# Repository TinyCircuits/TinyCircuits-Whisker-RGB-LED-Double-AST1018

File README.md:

# TinyCircuits Wireling RGB LED
# AST1018 Rev2

The design files are located under design_files/ for the TinyCircuits AST1018 Rev 2 PCB. This is a Wireling board which features the SK6812 Serial RGB LED to add a variety of bright colors to any project. Includes an additional connector for the option of connecting more RGB LED Wirelings.

Format is in Cadsoft Eagle format - Eagle version 6.2 was used for the original design.

For more infomation on this, check out the product page at TinyCircuits.com

# License:

Design by TinyCircuits.
All design files are released under the Creative Commons Attribution Share-Alike 3.0 License, see the following link for details: http://creativecommons.org/licenses/by-sa/3.0

All text above must be included in any redistribution or derived design

This project uses designs and concepts developed as part of the Arduino project and the LilyPad project.  The TinyCircuits design files themselves (schematics, PCB and libraries) are not directly derived from these works' design files and have been created new, however the concepts and basic architecture behind the TinyDuino and TinyLily products are derived and we thank the hard work of the organizations below for their contributions to open-source hardware:
  
Original Arduino Uno Design by Team Arduino

LilyPad Arduino Design by Leah Buechley and Sparkfun Electronics

Please support the open-source hardware community

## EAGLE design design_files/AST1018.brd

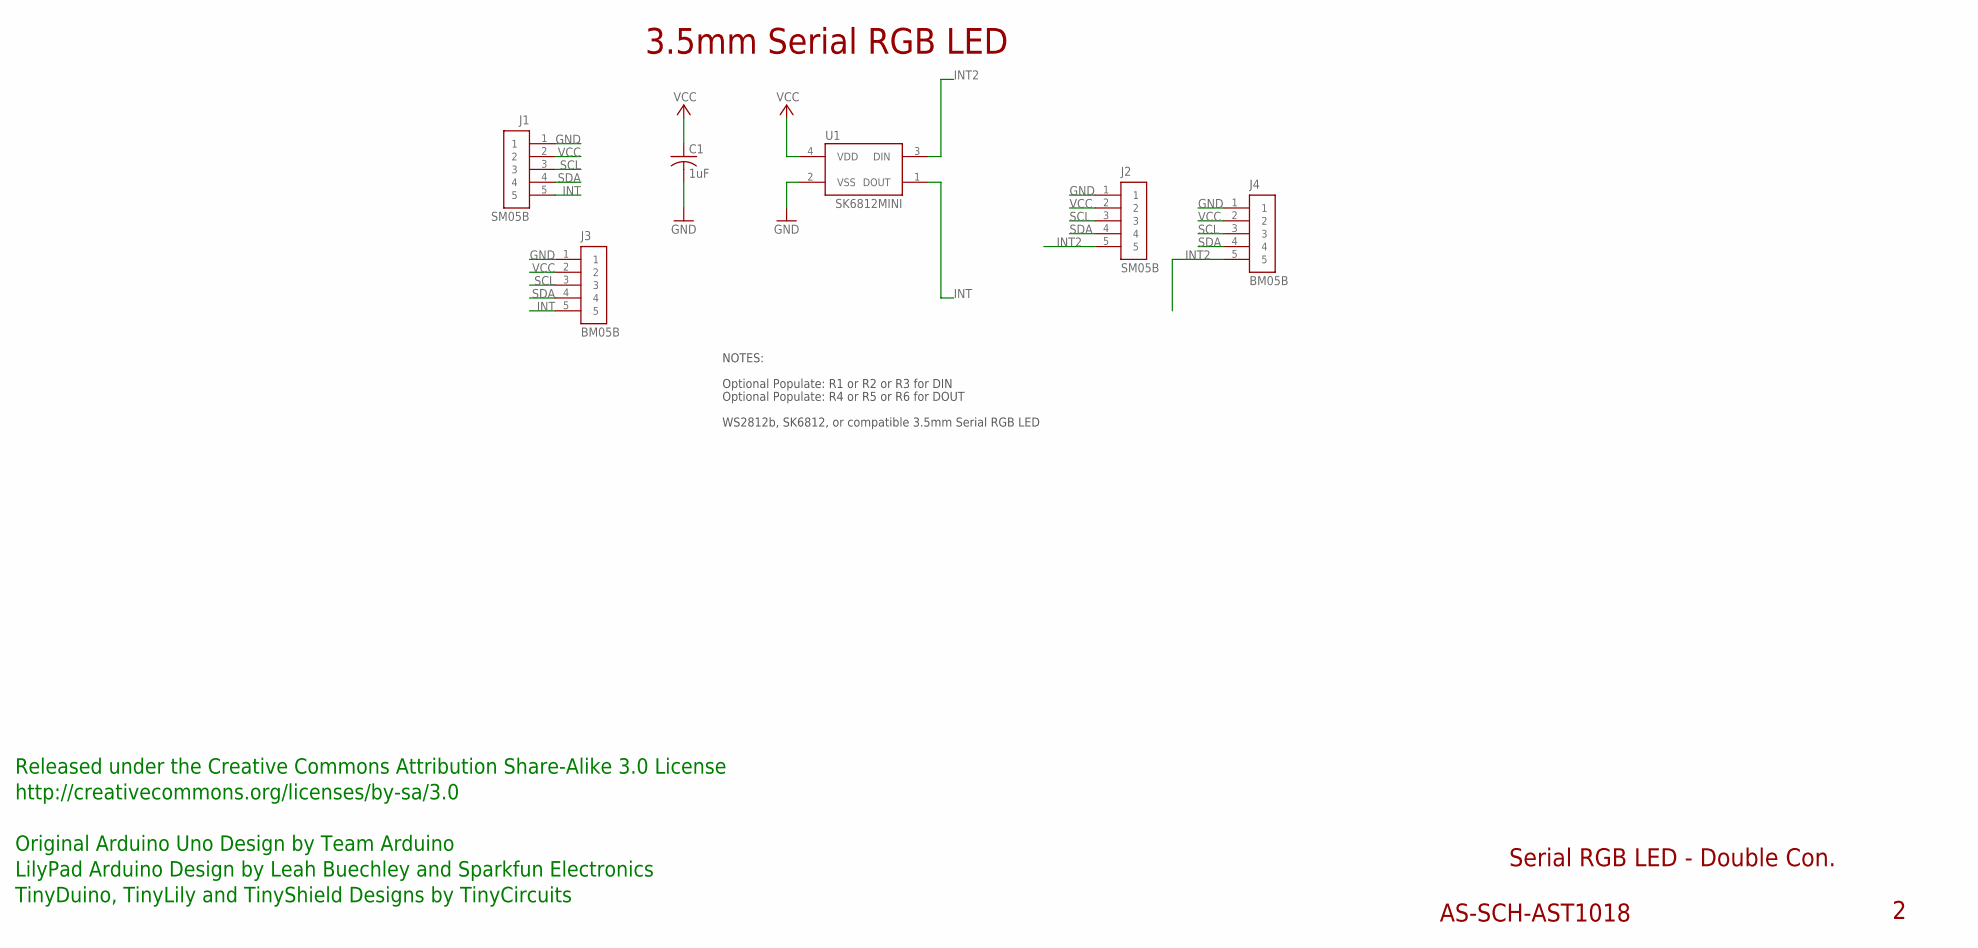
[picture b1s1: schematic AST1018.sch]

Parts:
C1: 1uF; C0603
J1, J2: SM05B; JST_SH_5X1
J3: BM05B; JST_SH_5X1_VERT
J4: BM05B; JST_SH_5X1_VERT; PARTNO AS-ITM-00391
U1: SK6812MINI

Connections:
GND: C1.2, J1.1, J2.1, J3.1, J4.1, U1.2 (VSS)
INT: J1.5, J3.5, U1.1 (DOUT)
INT2: J2.5, J4.5, U1.3 (DIN)
SCL: J1.3, J2.3, J3.3, J4.3
SDA: J1.4, J2.4, J3.4, J4.4
VCC: C1.1, J1.2, J2.2, J3.2, J4.2, U1.4 (VDD)

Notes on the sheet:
Serial RGB LED - Double Con.
AS-SCH-AST1018
3.5mm Serial RGB LED
Released under the Creative Commons Attribution Share-Alike 3.0 License
http://creativecommons.org/licenses/by-sa/3.0
Original Arduino Uno Design by Team Arduino
TinyDuino, TinyLily and TinyShield Designs by TinyCircuits
LilyPad Arduino Design by Leah Buechley and Sparkfun Electronics
NOTES:
Optional Populate: R4 or R5 or R6 for DOUT
Optional Populate: R1 or R2 or R3 for DIN
WS2812b, SK6812, or compatible 3.5mm Serial RGB LED

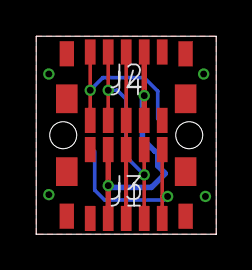
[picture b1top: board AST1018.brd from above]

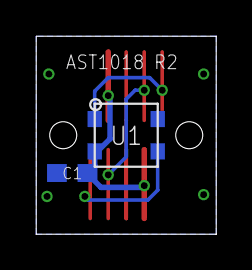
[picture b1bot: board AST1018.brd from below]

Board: 2 copper layers, 10.0 x 11.0 mm, 7 parts (2 on the bottom side), 6 nets.

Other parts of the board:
U$1: DOCFIELD-TINYCIRCUITS-PCB

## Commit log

2019-07-30 updated to use Port 0
2019-08-05 added datasheet
2019-10-18 Update program
2019-10-18 FastLED library
2019-12-02 images
2019-12-04 colorful code
2019-12-17 updated documentation
2020-01-02 fix image rotation
2020-02-04 mass image update
2020-08-14 Add CAD data
